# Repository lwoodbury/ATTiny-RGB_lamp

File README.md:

# ATTiny-RGB_lamp
 Programming an ATTiny84 with Arduino to make an RGB mood lamp

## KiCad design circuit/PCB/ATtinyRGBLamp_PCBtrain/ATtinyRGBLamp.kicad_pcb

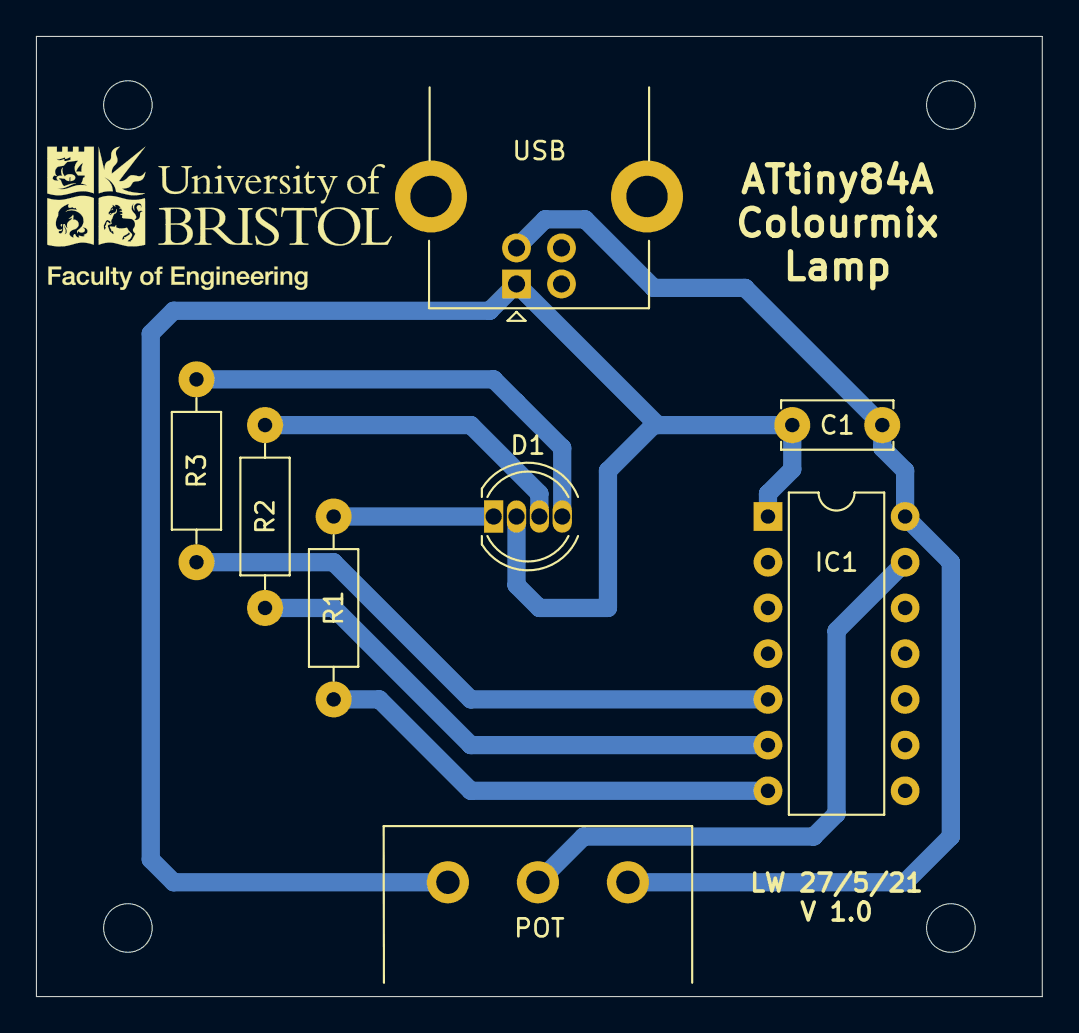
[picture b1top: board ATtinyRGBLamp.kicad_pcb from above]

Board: 2 copper layers, 55.9 x 53.3 mm, 8 parts (0 on the bottom side), 9 nets.

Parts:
C1: 100nF; C_Disc_D6.0mm_W2.5mm_P5.00mm
D1: LED_RGBA; LED_D5.0mm-4_RGB
IC1: ATtiny84A-PU; DIP-14_W7.62mm
POT: 10K POT; Potentiometer_Omeg_PC16BU_Horizontal
R1: 150R; R_Axial_DIN0207_L6.3mm_D2.5mm_P10.16mm_Horizontal
R2, R3: 100R; R_Axial_DIN0207_L6.3mm_D2.5mm_P10.16mm_Horizontal
USB: USB_B; USB_B_Lumberg_2411_02_Horizontal

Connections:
+5V: C1.2, D1.2, IC1.1, POT.1, USB.1
GND: C1.1, IC1.14, POT.3, USB.4
unnamed: D1.1, R1.1
unnamed: D1.3, R2.1
unnamed: D1.4, R3.1
unnamed: IC1.5, R3.2
unnamed: IC1.6, R2.2
unnamed: IC1.7, R1.2
unnamed: IC1.13, POT.2

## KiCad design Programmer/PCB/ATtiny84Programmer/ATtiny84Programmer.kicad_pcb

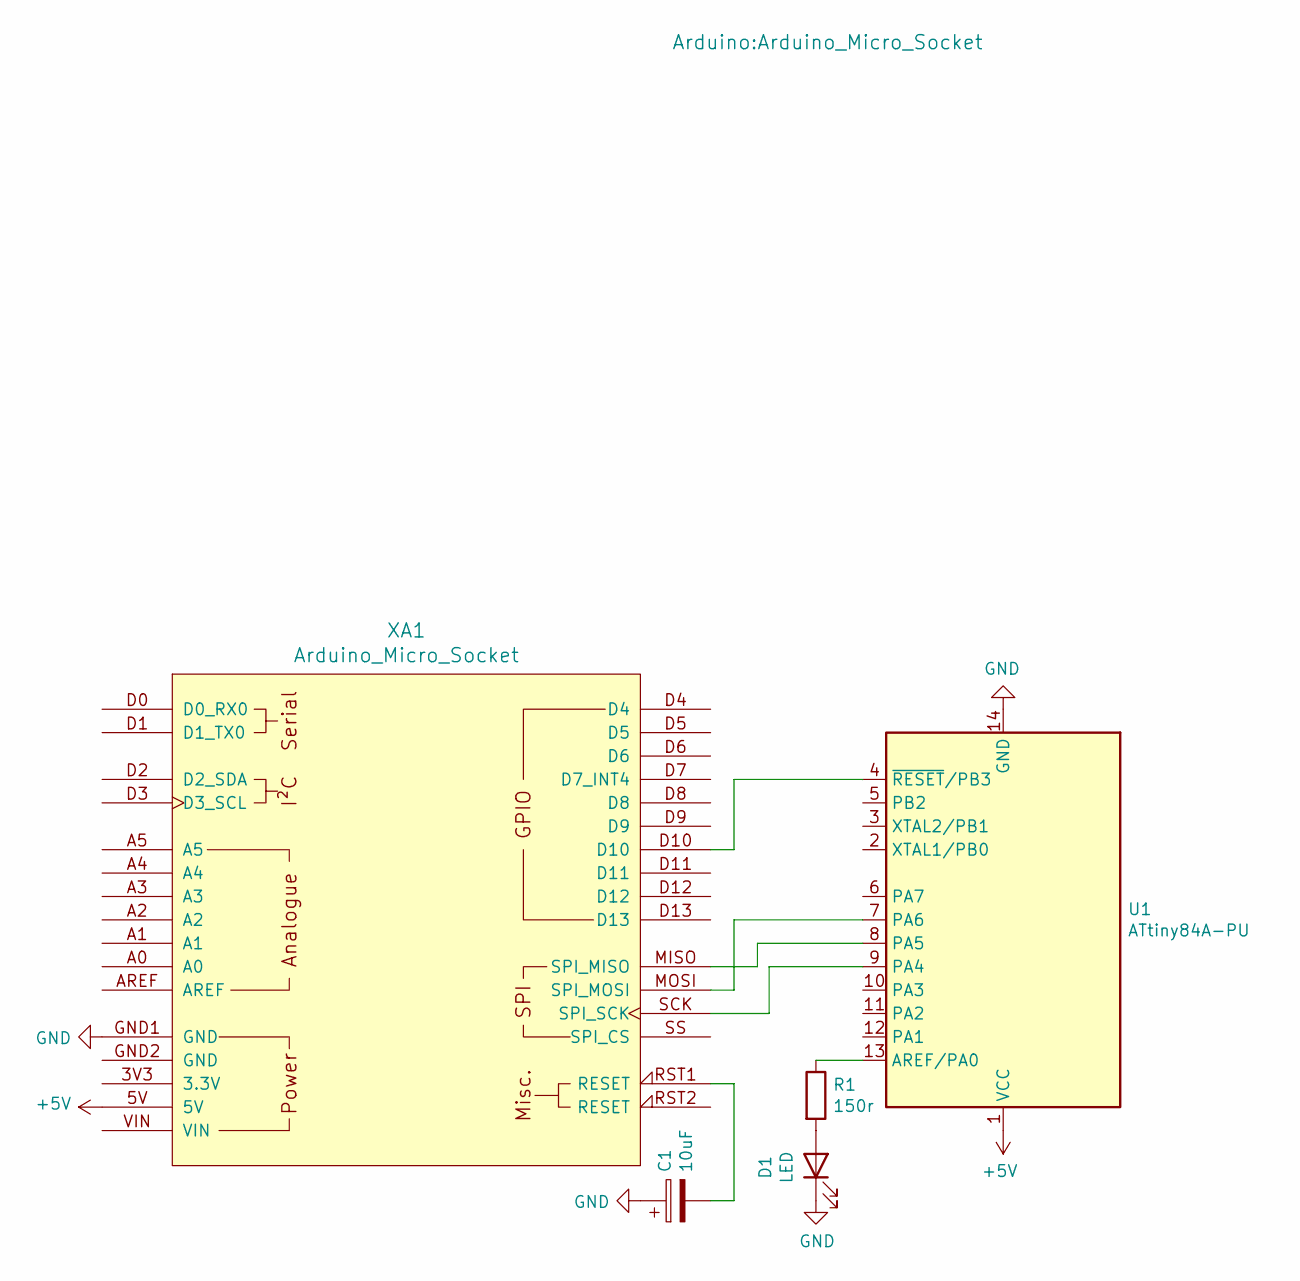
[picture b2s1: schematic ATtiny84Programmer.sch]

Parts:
C1: 10uF; CP_Radial_D5.0mm_P2.50mm
D1: LED; LED_D5.0mm
R1: 150r; R_Axial_DIN0207_L6.3mm_D2.5mm_P10.16mm_Horizontal
U1: ATtiny84A-PU; DIP-14_W7.62mm
XA1: Arduino_Micro_Socket

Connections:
+5V: U1.1 (VCC), XA1.5V
GND: C1.1, D1.1 (K), U1.14 (GND), XA1.GND1 (GND)
unnamed: C1.2, XA1.RST1 (RESET)
unnamed: D1.2 (A), R1.2
unnamed: R1.1, U1.13 (AREF/PA0)
unnamed: U1.4 (~RESET~/PB3), XA1.D10
unnamed: U1.7 (PA6), XA1.MOSI (SPI_MOSI)
unnamed: U1.8 (PA5), XA1.MISO (SPI_MISO)
unnamed: U1.9 (PA4), XA1.SCK (SPI_SCK)

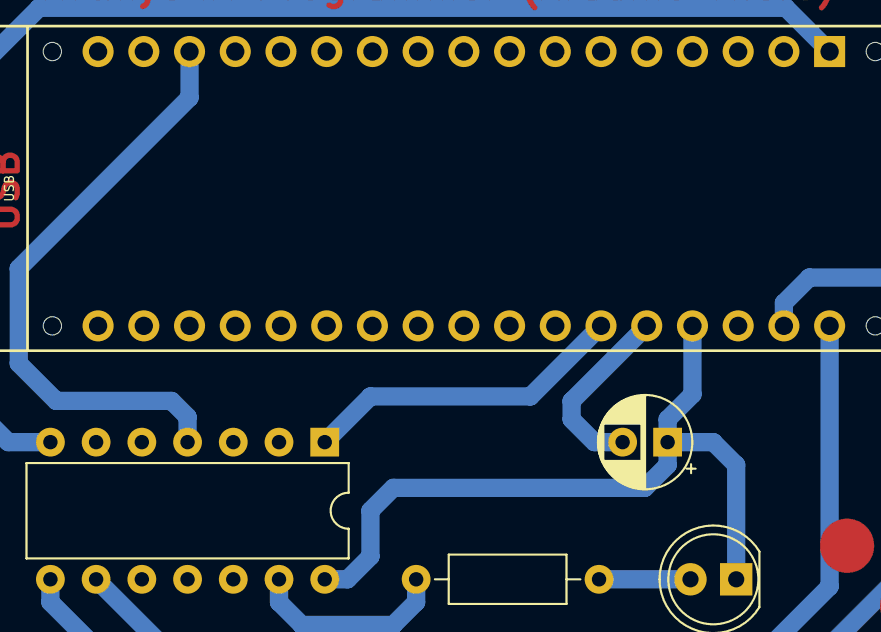
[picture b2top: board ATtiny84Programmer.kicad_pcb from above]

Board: 2 copper layers, 5 parts (0 on the bottom side), 9 nets.

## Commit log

2022-06-08 resize image
2022-06-08 add PCB img
2022-06-08 Resize PCB img
